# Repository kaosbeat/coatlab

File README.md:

# kicad Python env

- enable system environment  
`pyenv global system`  

install whatever package needed

debian prohibits the use of pip for system, unless used with --break-system-packages
eg. `pip3 --break-system-packages install KicadModTree  `

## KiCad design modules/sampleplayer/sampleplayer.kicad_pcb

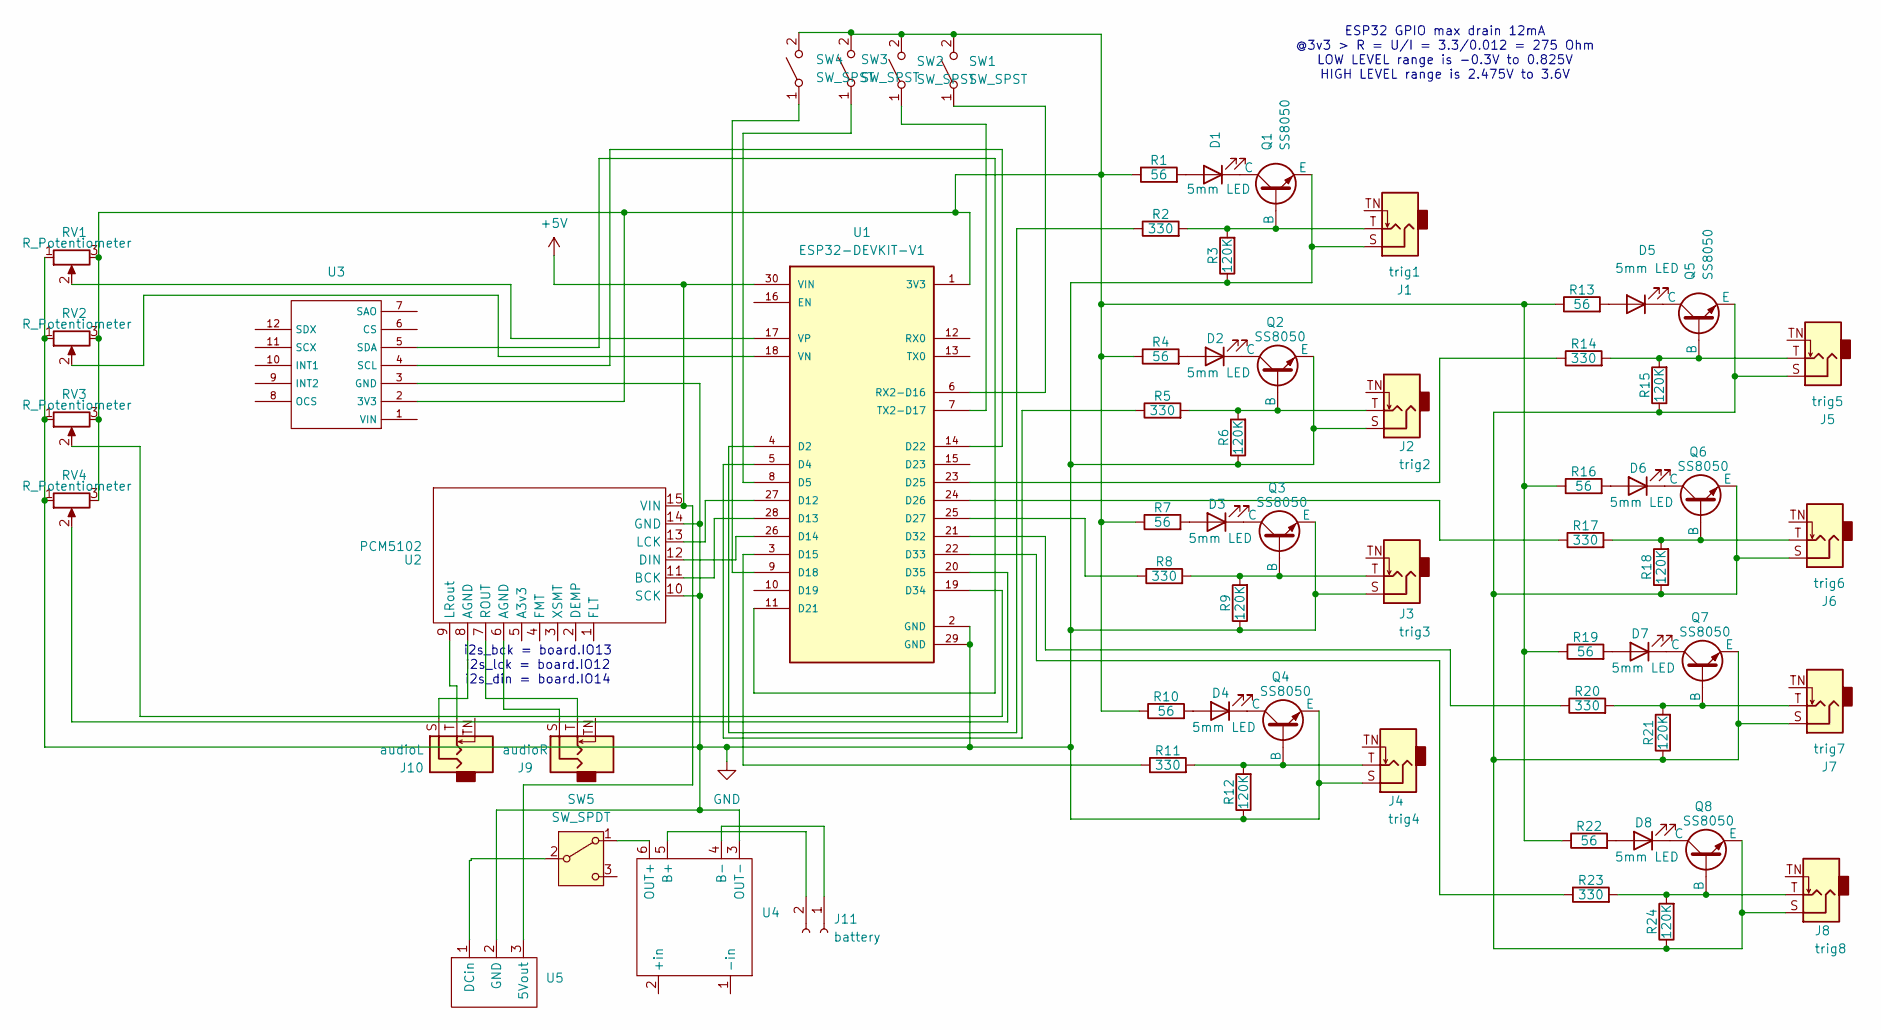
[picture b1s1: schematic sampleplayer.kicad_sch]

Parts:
D1, D2, D3, D4, D5, D6, D7, D8: 5mm LED; LED_D5.0mm
J1: trig1; Jack_3.5mm_QingPu_WQP-PJ301M-12_Vertical
J2: trig2; Jack_3.5mm_QingPu_WQP-PJ301M-12_Vertical
J3: trig3; Jack_3.5mm_QingPu_WQP-PJ301M-12_Vertical
J4: trig4; Jack_3.5mm_QingPu_WQP-PJ301M-12_Vertical
J5: trig5; Jack_3.5mm_QingPu_WQP-PJ301M-12_Vertical
J6: trig6; Jack_3.5mm_QingPu_WQP-PJ301M-12_Vertical
J7: trig7; Jack_3.5mm_QingPu_WQP-PJ301M-12_Vertical
J8: trig8; Jack_3.5mm_QingPu_WQP-PJ301M-12_Vertical
J9: audioR; Jack_3.5mm_QingPu_WQP-PJ301M-12_Vertical
J10: audioL; Jack_3.5mm_QingPu_WQP-PJ301M-12_Vertical
J11: battery; JST_PH_B2B-PH-K_1x02_P2.00mm_Vertical
Q1, Q2, Q3, Q4, Q5, Q6, Q7, Q8: SS8050; SOT-23-3
R1, R4, R7, R10, R13, R16, R19, R22: 56; R_0201_0603Metric
R2, R5, R8, R11, R14, R17, R20, R23: 330; R_0201_0603Metric
R3, R6, R9, R12, R15, R18, R21, R24: 120K; R_0201_0603Metric
RV1, RV2, RV3, RV4: R_Potentiometer; Potentiometer_Alps_RK09K_Single_Vertical
SW1, SW2, SW3, SW4: SW_SPST; SW_PUSH-12mm
SW5: SW_SPDT; 13x8mm_3pin
U1: ESP32-DEVKIT-V1; MODULE_ESP32_DEVKIT_V1; PARTREV N/A
U2: PCM5102
U3: BMI160
U4: TP4056
U5: DCDC5V

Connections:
+5V: U1.30 (VIN), U2.15 (VIN), U5.3 (5Vout)
GND: J1.S, J2.S, J3.S, J4.S, Q1.3 (E), Q2.3 (E), Q3.3 (E), Q4.3 (E), R3.1, R6.1, R9.1, R12.1, RV1.1, RV2.1, RV3.1, RV4.1, U1.2 (GND), U1.29 (GND), U2.10 (SCK), U2.14 (GND), U3.3 (GND), U4.3 (OUT-), U5.2 (GND)
unnamed: D1.2 (A), R1.2
unnamed: D1.1 (K), Q1.1 (C)
unnamed: D2.2 (A), R4.2
unnamed: D2.1 (K), Q2.1 (C)
unnamed: D3.2 (A), R7.2
unnamed: D3.1 (K), Q3.1 (C)
unnamed: D4.2 (A), R10.2
unnamed: D4.1 (K), Q4.1 (C)
unnamed: D5.2 (A), R13.2
unnamed: D5.1 (K), Q5.1 (C)
unnamed: D6.2 (A), R16.2
unnamed: D6.1 (K), Q6.1 (C)
unnamed: D7.2 (A), R19.2
unnamed: D7.1 (K), Q7.1 (C)
unnamed: D8.2 (A), R22.2
unnamed: D8.1 (K), Q8.1 (C)
unnamed: J9.S, U2.6 (AGND)
unnamed: J10.S, U2.8 (AGND)
unnamed: J11.1, U4.4 (B-)
unnamed: J11.2, U4.5 (B+)
unnamed: J1.T, Q1.2 (B), R2.2, R3.2
unnamed: J2.T, Q2.2 (B), R5.2, R6.2
unnamed: J3.T, Q3.2 (B), R8.2, R9.2
unnamed: J4.T, Q4.2 (B), R11.2, R12.2
unnamed: J5.T, Q5.2 (B), R14.2, R15.2
unnamed: J5.S, J6.S, J7.S, J8.S, Q5.3 (E), Q6.3 (E), Q7.3 (E), Q8.3 (E), R15.1, R18.1, R21.1, R24.1
unnamed: J6.T, Q6.2 (B), R17.2, R18.2
unnamed: J7.T, Q7.2 (B), R20.2, R21.2
unnamed: J8.T, Q8.2 (B), R23.2, R24.2
unnamed: SW1.1 (A), U1.6 (RX2-D16)
unnamed: R1.1, R4.1, R7.1, R10.1, R13.1, R16.1, R19.1, R22.1, RV1.3, RV2.3, RV3.3, RV4.3, SW1.2 (B), SW2.2 (B), SW3.2 (B), SW4.2 (B), U1.1 (3V3), U3.2 (3V3)
unnamed: SW2.1 (A), U1.7 (TX2-D17)
unnamed: SW3.1 (A), U1.8 (D5)
unnamed: SW4.1 (A), U1.9 (D18)
unnamed: SW5.1 (A), U4.6 (OUT+)
unnamed: SW5.2 (B), U5.1 (DCin)
unnamed: R2.1, U1.4 (D2)
unnamed: R5.1, U1.5 (D4)
unnamed: U1.27 (D12), U2.13 (LCK)
unnamed: U1.28 (D13), U2.11 (BCK)
unnamed: U1.26 (D14), U2.12 (DIN)
unnamed: R11.1, U1.3 (D15)
unnamed: U1.11 (D21), U3.5 (SDA)
unnamed: U1.14 (D22), U3.4 (SCL)
unnamed: R14.1, U1.23 (D25)
unnamed: R17.1, U1.24 (D26)
unnamed: R8.1, U1.25 (D27)
unnamed: R20.1, U1.21 (D32)
unnamed: R23.1, U1.22 (D33)
unnamed: RV3.2, U1.19 (D34)
unnamed: RV4.2, U1.20 (D35)
unnamed: RV2.2, U1.18 (VN)
unnamed: RV1.2, U1.17 (VP)
unnamed: J10.T, U2.9 (LRout)
unnamed: J9.T, U2.7 (ROUT)

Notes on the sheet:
i2s_bck = board.IO13 i2s_lck = board.IO12 i2s_din = board.IO14
ESP32 GPIO max drain 12mA @3v3 > R = U/I = 3.3/0.012 = 275 Ohm LOW LEVEL range is -0.3V to 0.825V HIGH LEVEL range is 2.475V to 3.6V

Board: 2 copper layers, 65 parts (4 on the bottom side), 57 nets, no tracks yet.

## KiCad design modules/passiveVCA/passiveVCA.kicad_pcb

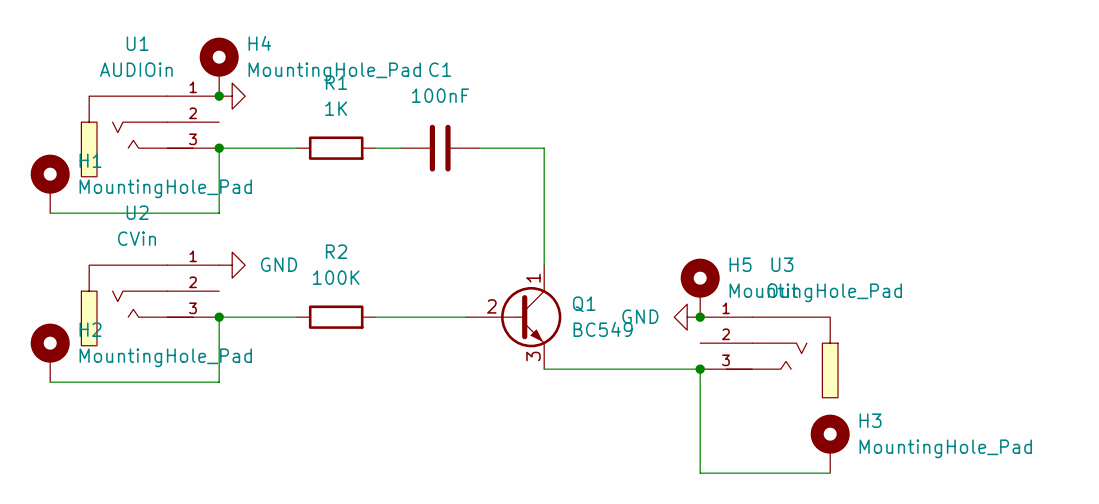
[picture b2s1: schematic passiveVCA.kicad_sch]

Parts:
C1: 100nF; C_0402_1005Metric
H1, H2, H3, H4, H5: MountingHole_Pad; MountingHole_2.2mm_M2_Pad_TopBottom
Q1: BC549; TO-92_Inline
R1: 1K; R_0402_1005Metric
R2: 100K; R_0402_1005Metric
U1: AUDIOin; AUDIO-TH_PJ-313B; LCSC C22435690
U2: CVin; AUDIO-TH_PJ-313B; LCSC C22435690
U3: Out; AUDIO-TH_PJ-313B; LCSC C22435690

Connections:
GND: H4.1, H5.1, U1.1, U2.1, U3.1
unnamed: C1.1, R1.2
unnamed: H1.1, R1.1, U1.3
unnamed: H2.1, R2.1, U2.3
unnamed: Q1.2 (B), R2.2
unnamed: C1.2, Q1.1 (C)
unnamed: H3.1, Q1.3 (E), U3.3

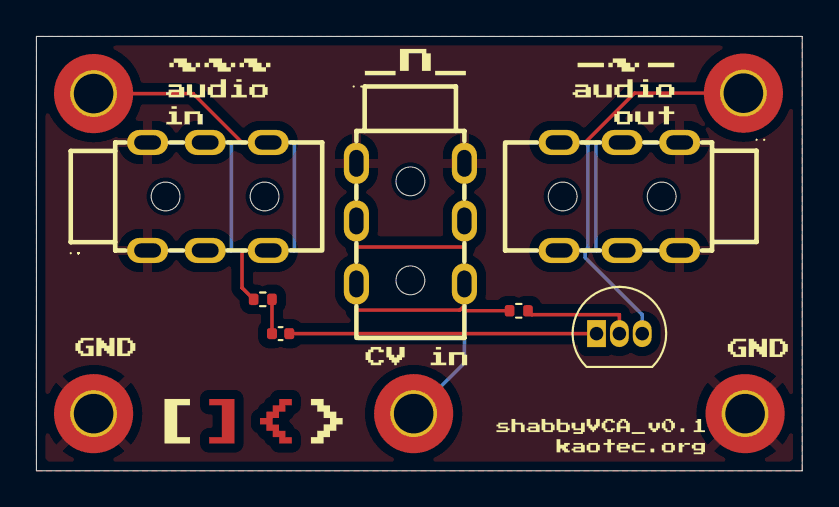
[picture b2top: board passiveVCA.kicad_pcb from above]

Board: 2 copper layers, 42.5 x 24.1 mm, 12 parts (0 on the bottom side), 7 nets.

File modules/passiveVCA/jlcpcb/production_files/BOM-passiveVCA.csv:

Comment,Designator,Footprint,LCSC,Quantity
1K,R1,R_0402_1005Metric,C11702,1
100nF,C1,C_0402_1005Metric,C1525,1
AUDIOin,"U1,U2,U3",AUDIO-TH_PJ-313B,C22435690,3
100K,R2,R_0402_1005Metric,C25741,1
BC549,Q1,TO-92_Inline,C5455746,1

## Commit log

2025-02-03 code
2025-02-07 adding civiati workflow fro reference:
2025-02-07 scienmcesamples
2025-02-17 blkah
2025-07-14 ignore
2025-07-14 upodates
2025-07-23 sampleplayer update
2025-08-13 sampleplayerupdate
2025-08-21 sequencer
